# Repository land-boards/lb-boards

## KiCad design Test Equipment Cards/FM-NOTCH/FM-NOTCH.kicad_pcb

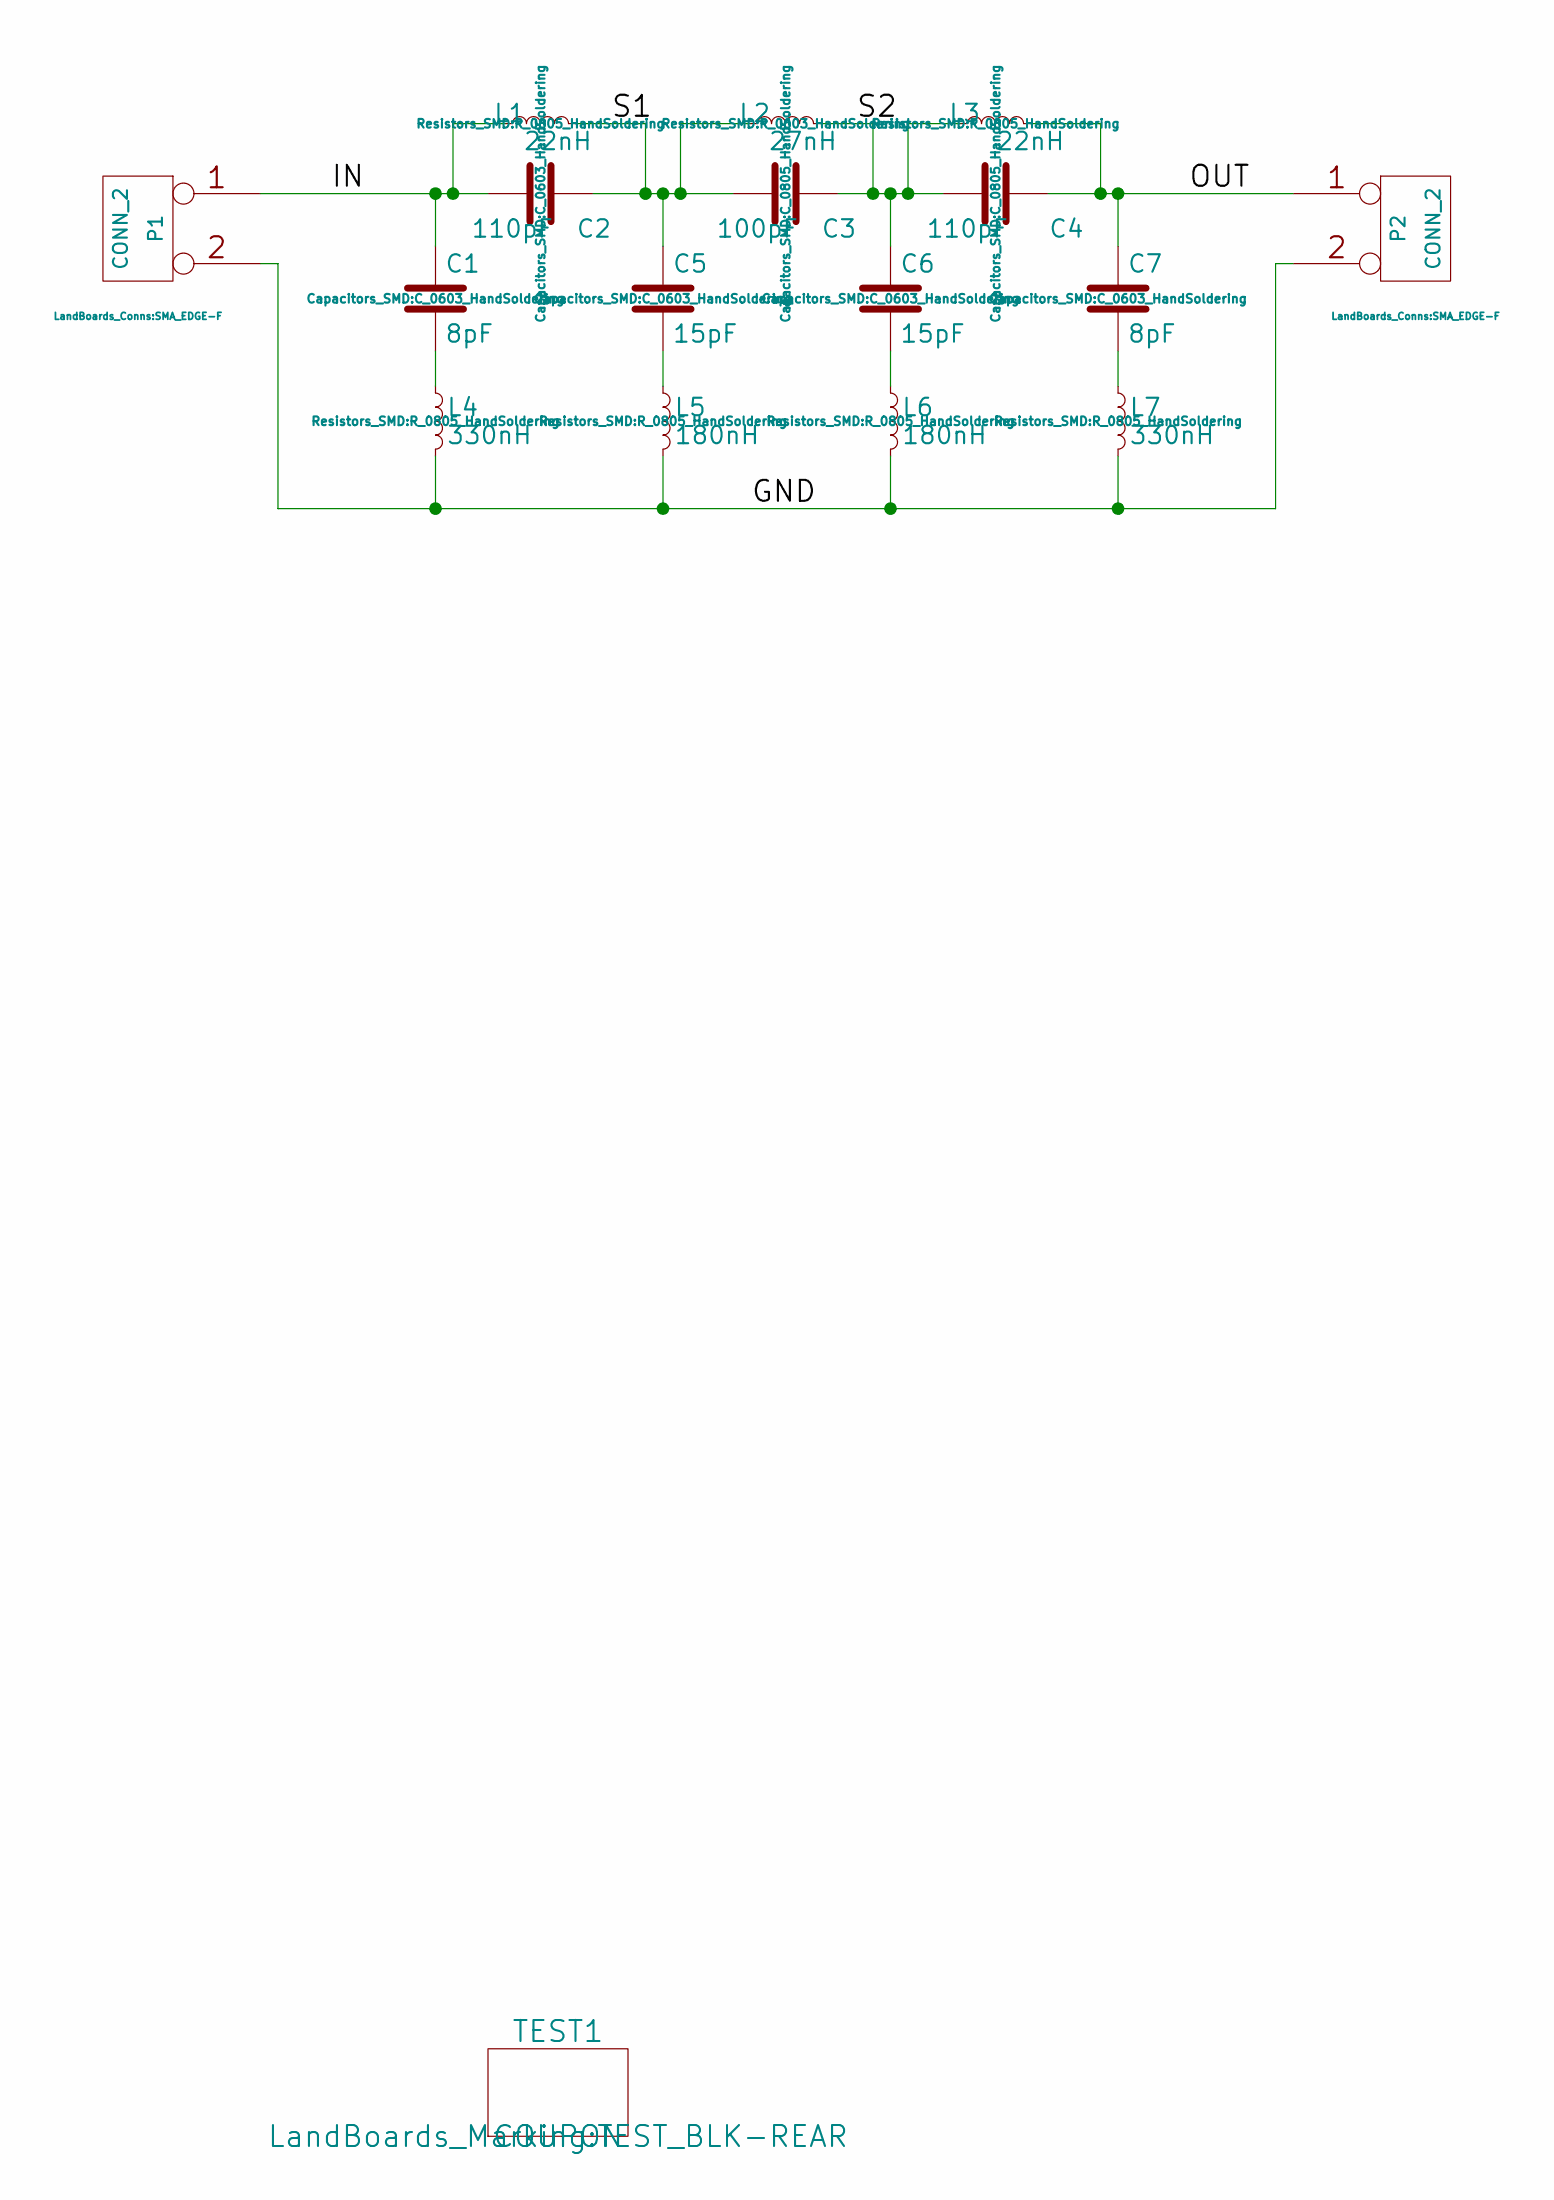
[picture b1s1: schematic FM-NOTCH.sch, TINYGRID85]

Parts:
C1, C7: 8pF; C_0603_HandSoldering
C2: 110pF; C_0603_HandSoldering
C3: 100pF; C_0805_HandSoldering
C4: 110pF; C_0805_HandSoldering
C5, C6: 15pF; C_0603_HandSoldering
L1, L3: 22nH; R_0805_HandSoldering
L2: 27nH; R_0603_HandSoldering
L4, L7: 330nH; R_0805_HandSoldering
L5, L6: 180nH; R_0805_HandSoldering
P1, P2: CONN_2; SMA_EDGE-F
TEST1: COUPON; TEST_BLK-REAR

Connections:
/GND: L4.2, L5.2, L6.2, L7.2, P1.2 (PM), P2.2 (PM)
/IN: C1.1, C2.2, L1.1, P1.1
/OUT: C4.1, C7.1, L3.2, P2.1
/S1: C2.1, C3.2, C5.1, L1.2, L2.1
/S2: C3.1, C4.2, C6.1, L2.2, L3.1
unnamed: C1.2, L4.1
unnamed: C5.2, L5.1
unnamed: C6.2, L6.1
unnamed: C7.2, L7.1

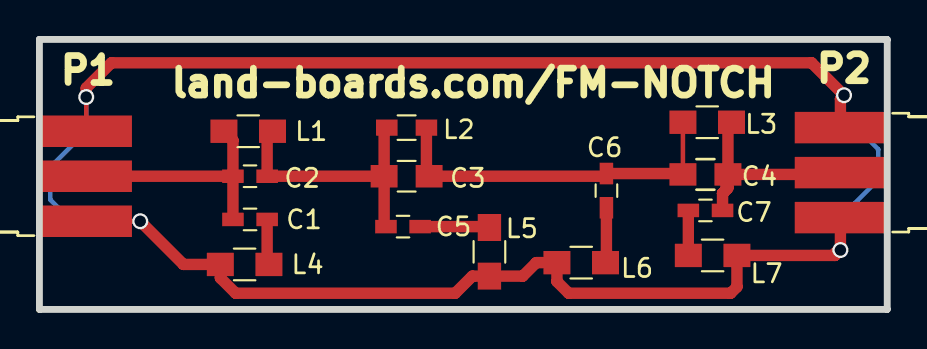
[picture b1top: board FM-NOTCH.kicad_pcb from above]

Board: 2 copper layers, 47.1 x 15.0 mm, 17 parts (0 on the bottom side), 9 nets.

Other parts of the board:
TEST: COUPON; TEST_BLK-REAR

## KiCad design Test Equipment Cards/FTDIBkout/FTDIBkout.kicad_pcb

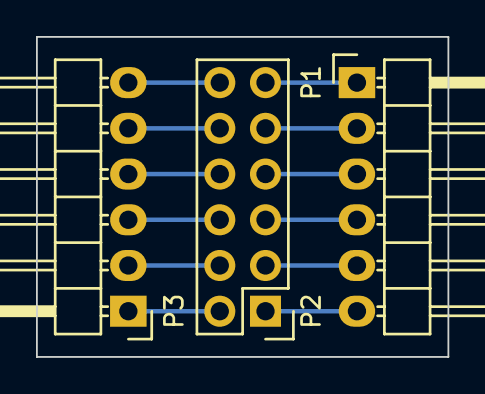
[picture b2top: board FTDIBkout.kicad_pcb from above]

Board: 2 copper layers, 22.9 x 17.8 mm, 3 parts (0 on the bottom side), 12 nets.

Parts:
P1, P3: CONN_01X06; Pin_Header_Angled_1x06
P2: CONN_02X06; Pin_Header_Straight_2x06

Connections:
unnamed: P1.1, P2.11
unnamed: P1.2, P2.9
unnamed: P1.3, P2.7
unnamed: P1.4, P2.5
unnamed: P1.5, P2.3
unnamed: P1.6, P2.1
unnamed: P2.2, P3.1
unnamed: P2.4, P3.2
unnamed: P2.6, P3.3
unnamed: P2.8, P3.4
unnamed: P2.10, P3.5
unnamed: P2.12, P3.6

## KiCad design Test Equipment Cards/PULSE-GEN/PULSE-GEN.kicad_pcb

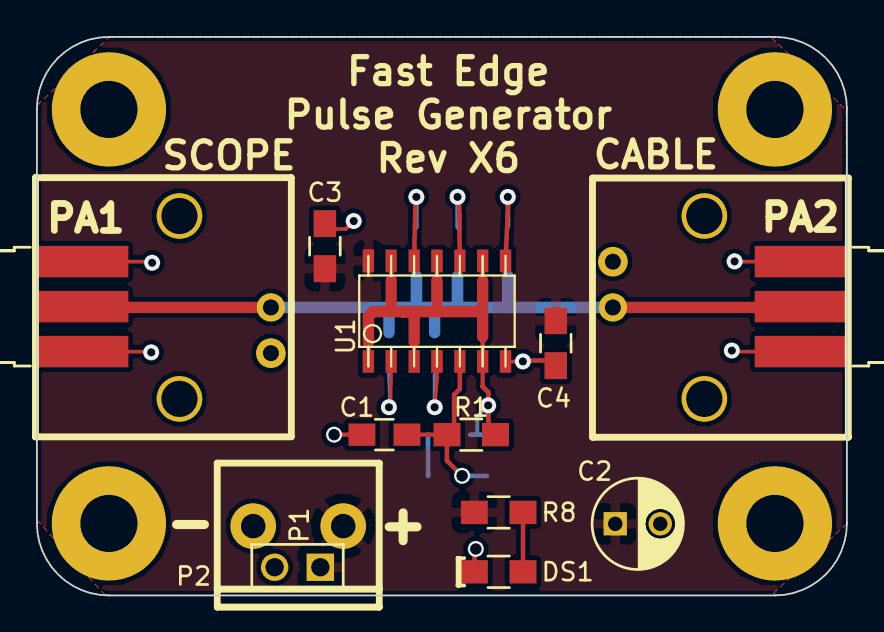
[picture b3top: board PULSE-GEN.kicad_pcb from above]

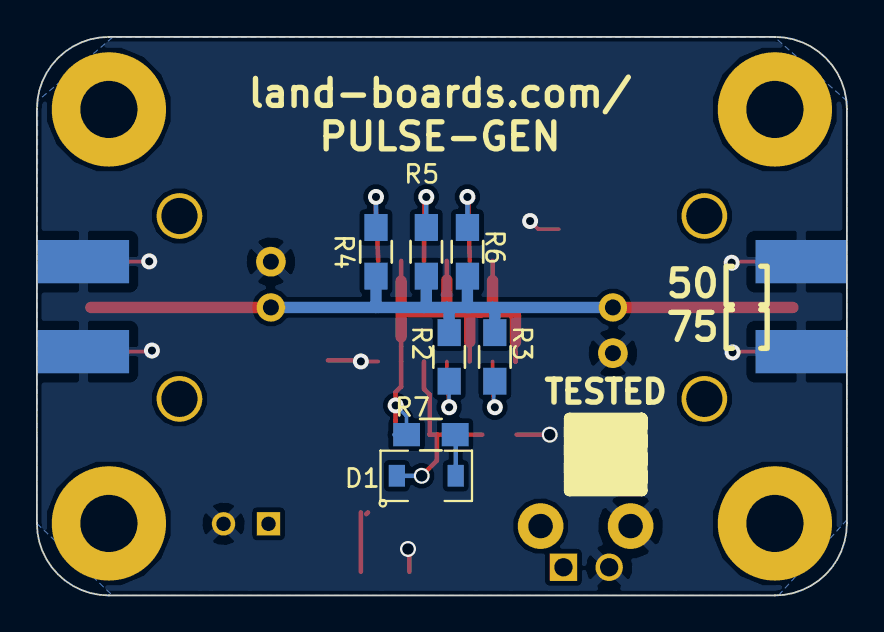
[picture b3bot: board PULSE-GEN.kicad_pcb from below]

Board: 2 copper layers, 45.0 x 31.0 mm, 26 parts (7 on the bottom side), 12 nets.

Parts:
C1: 47nF; C_0805_HandSoldering
C2: 47uF; C_Radial_D5_L11_P2.5
C3, C4: 0.1uF; C_0805_HandSoldering
D1: 1N4148; SOD-123
DS1: LED; R_0805_HandSoldering
MTG1, MTG2, MTG3, MTG4: CONN_1; MTG-4-40
P1: CONN_2; PIN_ARRAY_2X1
P2: CONN_2; TB2-5MM
PA1, PA2: SMA; SMA_EDGE-F
PB1, PB2: BNC; BNC-RT
R1: 33K; R_0805_HandSoldering
R2, R3, R4, R5, R6: 249; R_0805_HandSoldering
R7: 150; R_0805_HandSoldering
R8: 240; R_0805_HandSoldering
TESTED: VAL**; TEST_BLK-REAR
U1: 74AC14; so-14

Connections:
GND: C1.2, C2.2, C3.2, C4.2, DS1.2, P1.2, P2.2, PA1.2, PA2.2, PB1.2, PB2.2, U1.7
unnamed: C1.1, D1.1, R1.1, U1.5
unnamed: D1.2, R7.1
unnamed: DS1.1, R8.2
unnamed: PA1.1, PA2.1, PB1.1, PB2.1, R2.2, R3.2, R4.2, R5.2, R6.2
unnamed: R1.2, R7.2, U1.1, U1.3, U1.6, U1.9, U1.11, U1.13
unnamed: R2.1, U1.4
unnamed: R3.1, U1.2
unnamed: R4.1, U1.8
unnamed: R5.1, U1.10
unnamed: R6.1, U1.12
VCC: C2.1, C3.1, C4.1, P1.1, P2.1, R8.1, U1.14

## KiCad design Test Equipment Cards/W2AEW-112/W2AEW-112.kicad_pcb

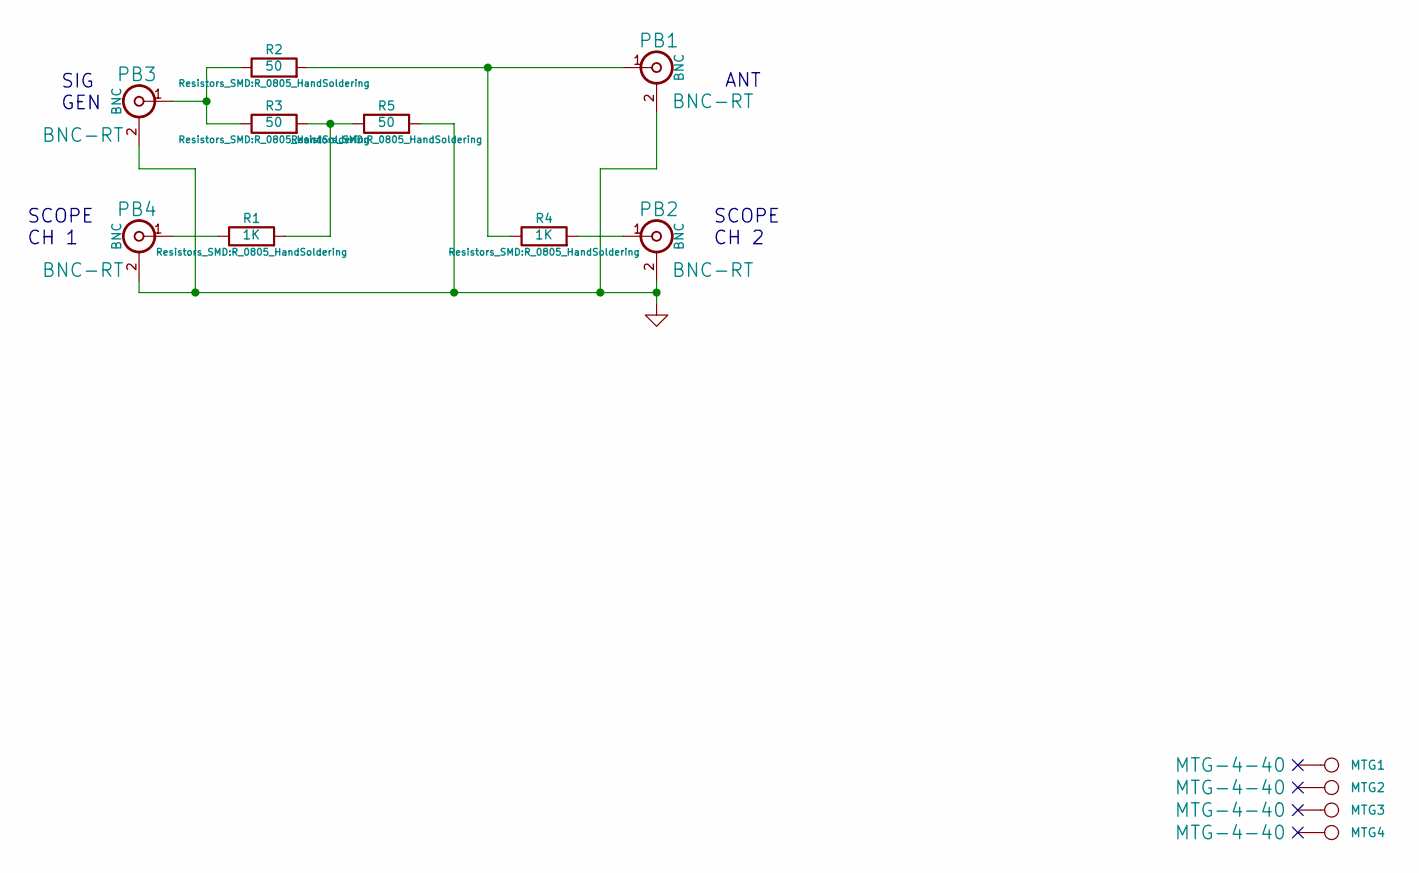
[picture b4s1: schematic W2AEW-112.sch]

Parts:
MTG1, MTG2, MTG3, MTG4: CONN_1; MTG-4-40
PB1, PB2, PB3, PB4: BNC; BNC-RT; MfgPN 31-5431-10RFX
R1, R4: 1K; R_0805_HandSoldering
R2, R3, R5: 50; R_0805_HandSoldering

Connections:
GND: PB1.2 (Ext), PB2.2 (Ext), PB3.2 (Ext), PB4.2 (Ext), R5.2
unnamed: PB1.1 (In), R2.2, R4.1
unnamed: PB2.1 (In), R4.2
unnamed: PB3.1 (In), R2.1, R3.1
unnamed: PB4.1 (In), R1.1
unnamed: R1.2, R3.2, R5.1

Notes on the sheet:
SIG GEN
ANT
SCOPE CH 1
SCOPE CH 2

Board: 2 copper layers, 13 parts (0 on the bottom side), 6 nets, no tracks yet.

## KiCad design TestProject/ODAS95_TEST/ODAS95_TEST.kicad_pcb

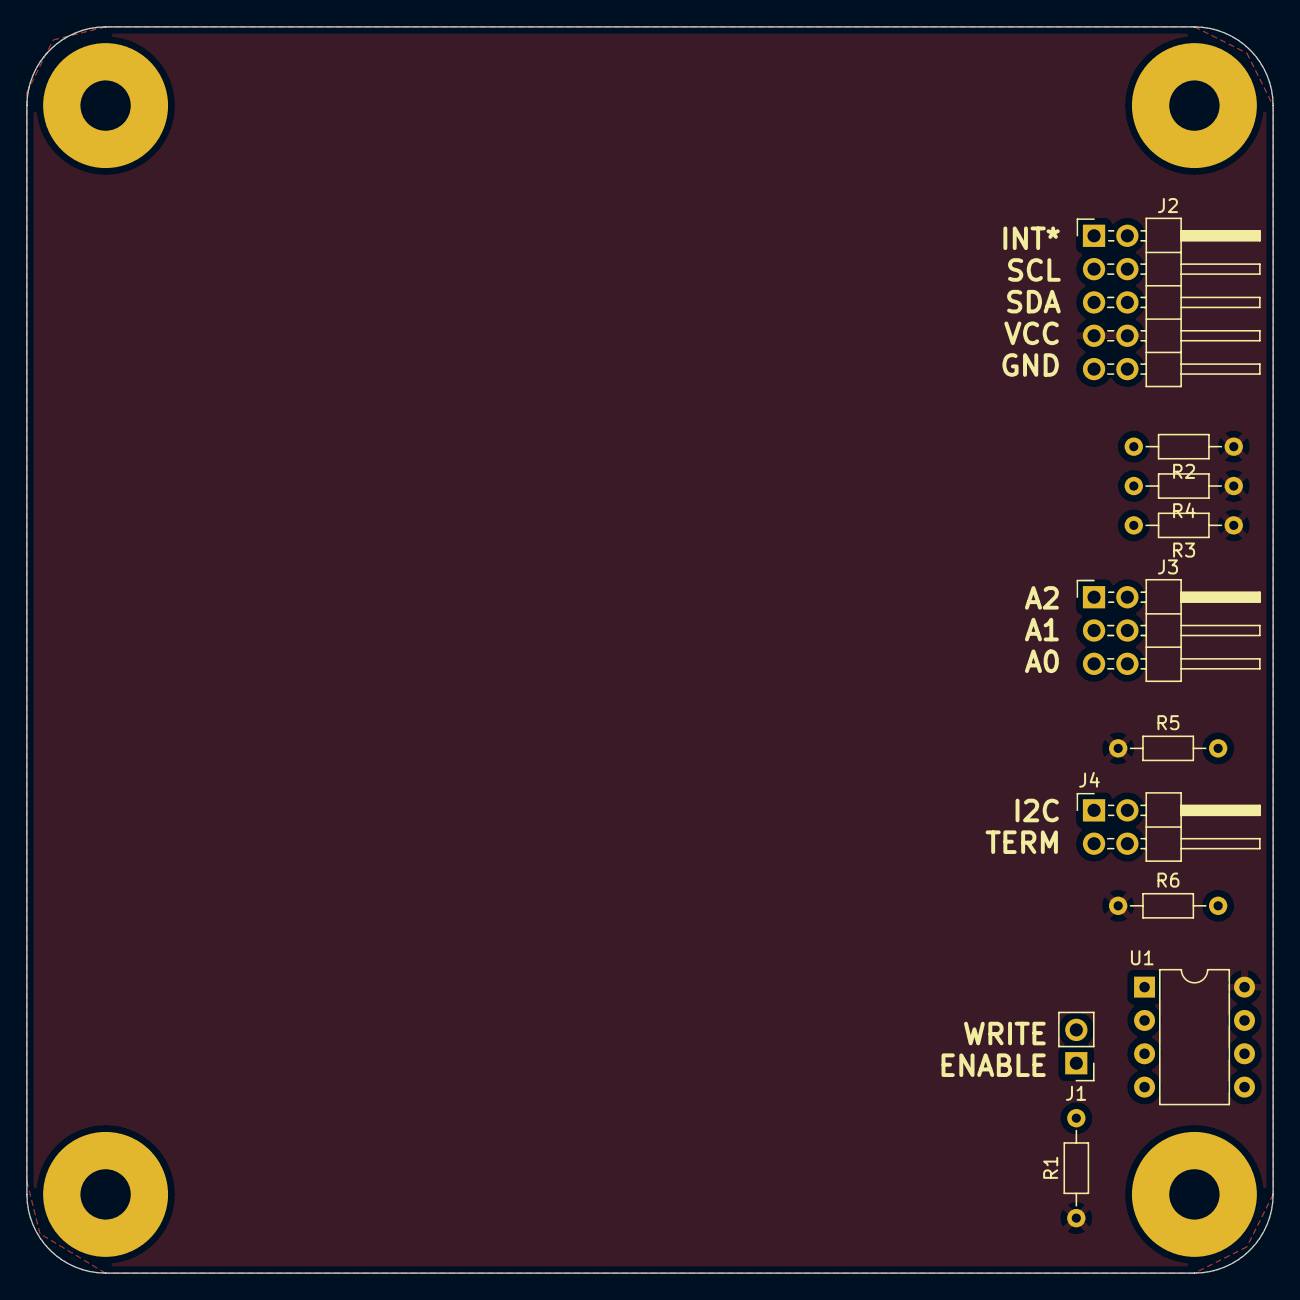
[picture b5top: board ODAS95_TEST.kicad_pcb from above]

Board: 2 copper layers, 95.0 x 95.0 mm, 16 parts (0 on the bottom side), 10 nets, no tracks yet.

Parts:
J1: Conn_01x02; PinHeader_1x02_P2.54mm_Vertical
J2: Conn_02x05_Odd_Even; PinHeader_2x05_P2.54mm_Horizontal
J3: Conn_02x03_Counter_Clockwise; PinHeader_2x03_P2.54mm_Horizontal
J4: Conn_02x02_Odd_Even; PinHeader_2x02_P2.54mm_Horizontal
MTG1, MTG2, MTG3, MTG4: MTG_HOLE; MTG-6-32
R1: 1K; R_Axial_DIN0204_L3.6mm_D1.6mm_P7.62mm_Horizontal
R2, R3, R4, R5, R6: 2.2K; R_Axial_DIN0204_L3.6mm_D1.6mm_P7.62mm_Horizontal
TEST1: TEST_COUPON; TEST_BLK-REAR
U1: 24lC024; DIP-8_W7.62mm

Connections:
/A0: J3.5, R4.2, U1.1 (A0)
/A1: J3.3, R3.2, U1.2 (A1)
/A2: J3.1, R2.2, U1.3 (A2)
/SCL: J2.3, J2.4, J4.3, U1.6 (SCL)
/SDA: J2.5, J2.6, J4.1, U1.5 (SDA)
GND: J1.2, J2.9, J2.10, J3.2, J3.4, J3.6, U1.4 (GND)
unnamed: J1.1, R1.2, U1.7 (~WP)
unnamed: J4.2, R5.2
unnamed: J4.4, R6.2
VCC: J2.7, J2.8, R1.1, R2.1, R3.1, R4.1, R5.1, R6.1, U1.8 (VCC)

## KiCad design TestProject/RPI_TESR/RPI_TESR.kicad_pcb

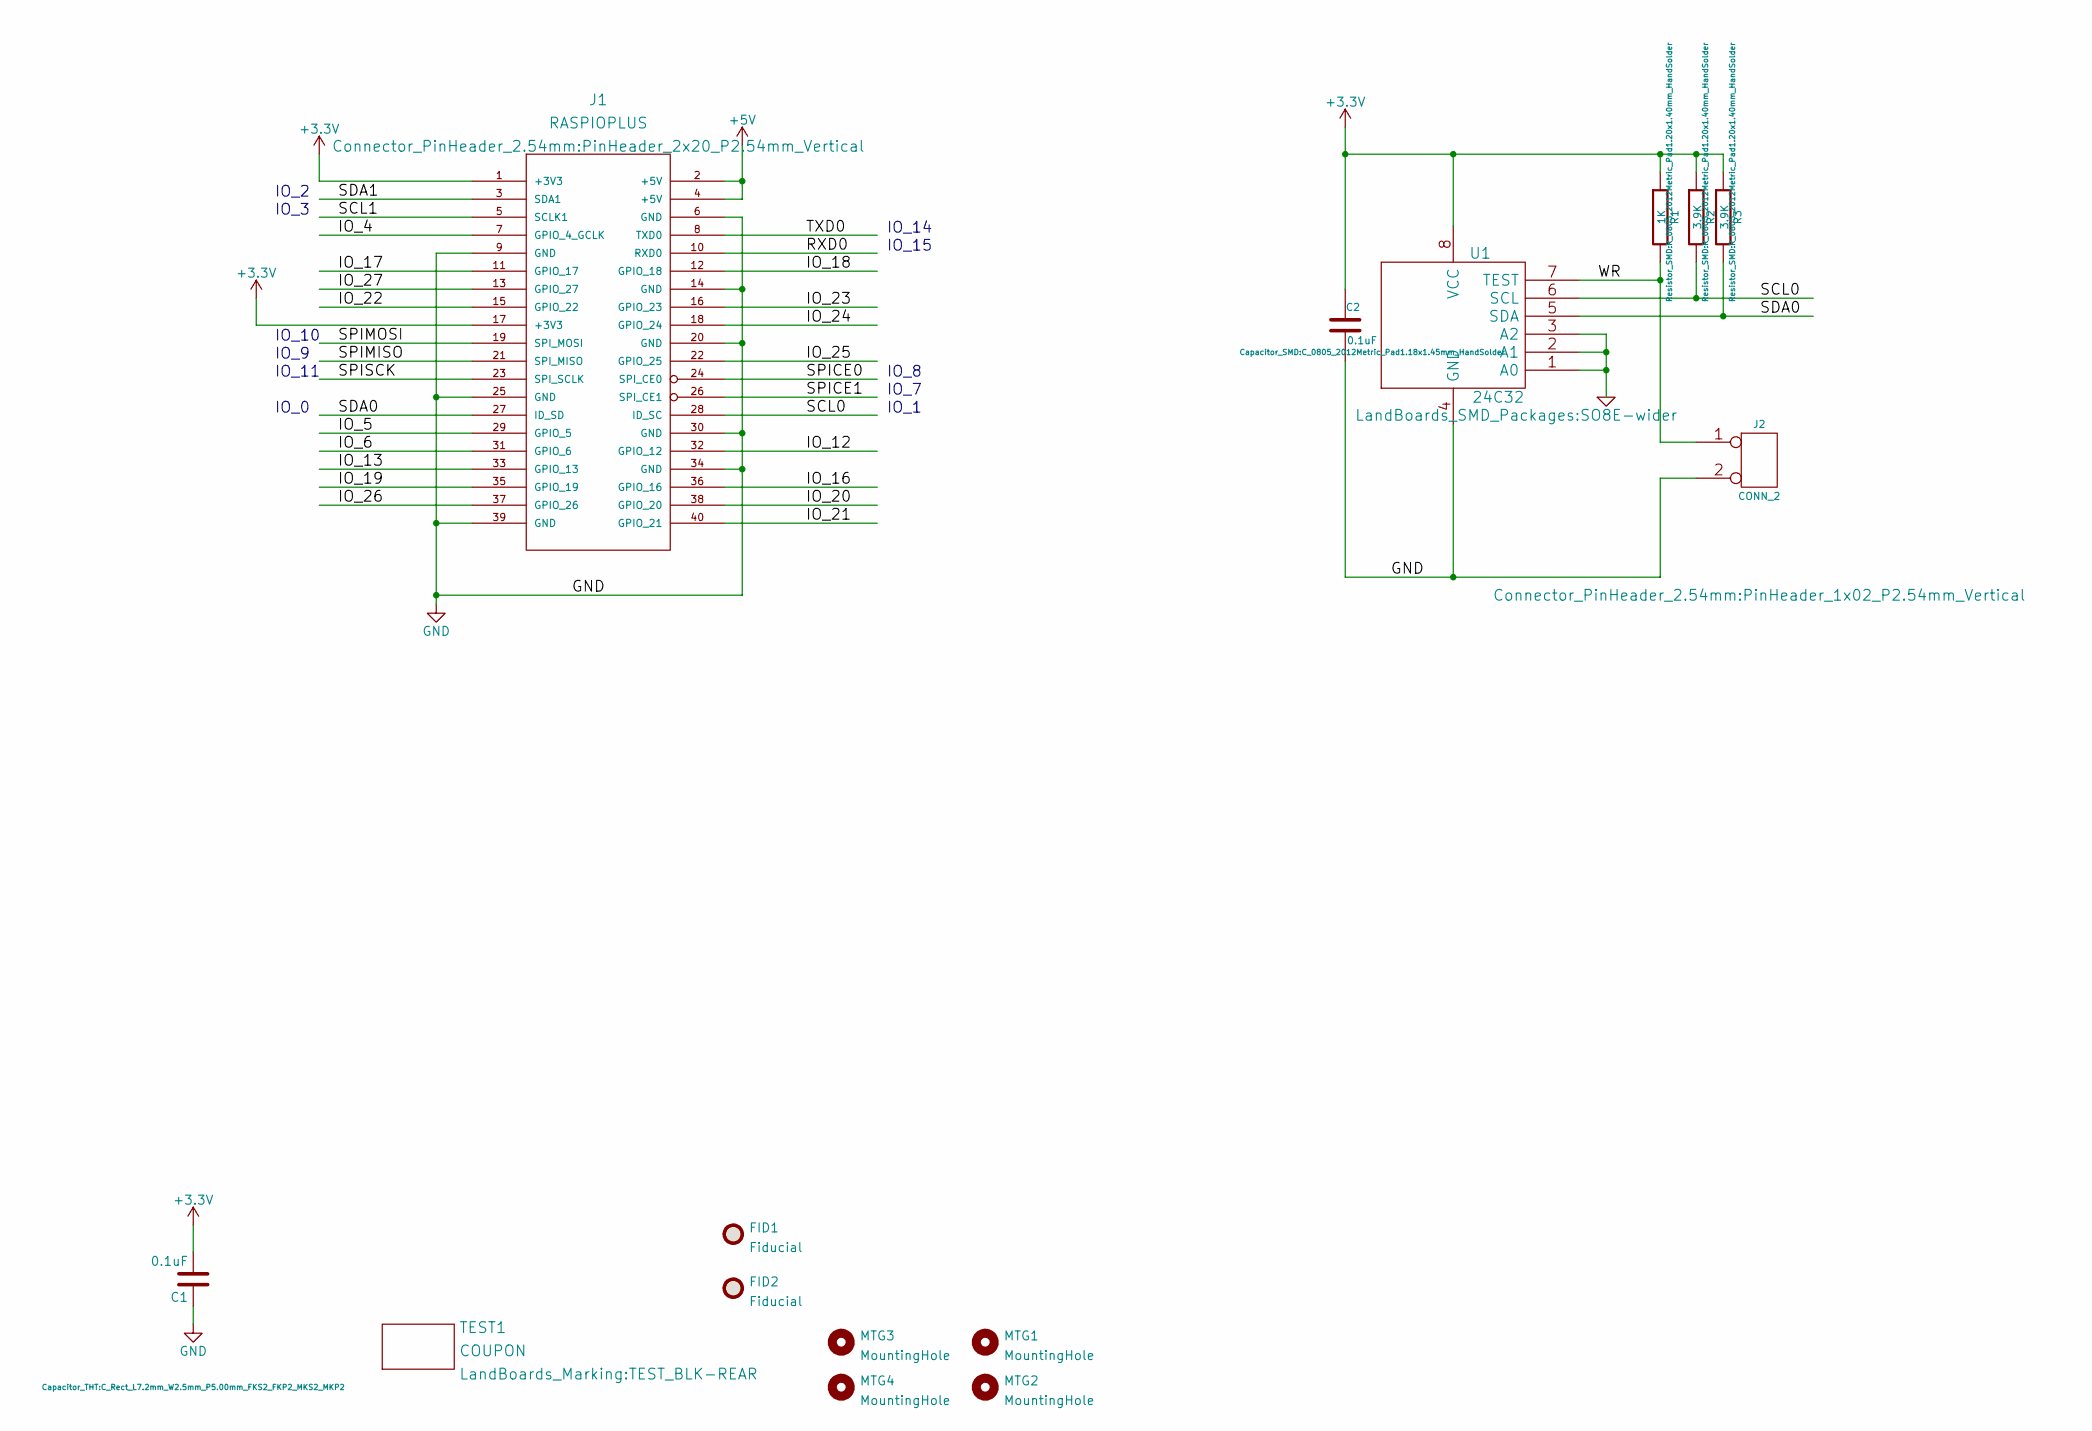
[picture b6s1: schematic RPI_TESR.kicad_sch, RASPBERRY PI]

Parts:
C1: 0.1uF; C_Rect_L7.2mm_W2.5mm_P5.00mm_FKS2_FKP2_MKS2_MKP2
C2: 0.1uF; C_0805_2012Metric_Pad1.18x1.45mm_HandSolder
FID1, FID2: Fiducial; Fiducial_0.75mm_Mask2.25mm
J1: RASPIOPLUS; PinHeader_2x20_P2.54mm_Vertical
J2: CONN_2; PinHeader_1x02_P2.54mm_Vertical
MTG1, MTG2, MTG3, MTG4: MountingHole; MountingHole_2.7mm_M2.5
R1: 1K; R_0805_2012Metric_Pad1.20x1.40mm_HandSolder
R2, R3: 3.9K; R_0805_2012Metric_Pad1.20x1.40mm_HandSolder
TEST1: COUPON; TEST_BLK-REAR
U1: 24C32; SO8E-wider

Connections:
+3V3: C1.2, C2.1, J1.1 (+3V3), J1.17 (+3V3), R1.1, R2.1, R3.1, U1.8 (VCC)
+5V: J1.2 (+5V), J1.4 (+5V)
/IO_4: J1.7 (GPIO_4_GCLK)
/IO_5: J1.29 (GPIO_5)
/IO_6: J1.31 (GPIO_6)
/IO_12: J1.32 (GPIO_12)
/IO_13: J1.33 (GPIO_13)
/IO_16: J1.36 (GPIO_16)
/IO_17: J1.11 (GPIO_17)
/IO_18: J1.12 (GPIO_18)
/IO_19: J1.35 (GPIO_19)
/IO_20: J1.38 (GPIO_20)
/IO_21: J1.40 (GPIO_21)
/IO_22: J1.15 (GPIO_22)
/IO_23: J1.16 (GPIO_23)
/IO_24: J1.18 (GPIO_24)
/IO_25: J1.22 (GPIO_25)
/IO_26: J1.37 (GPIO_26)
/IO_27: J1.13 (GPIO_27)
/RXD0: J1.10 (RXD0)
/SCL0: J1.28 (ID_SC), R2.2, U1.6 (SCL)
/SCL1: J1.5 (SCLK1)
/SDA0: J1.27 (ID_SD), R3.2, U1.5 (SDA)
/SDA1: J1.3 (SDA1)
/SPICE0: J1.24 (SPI_CE0)
/SPICE1: J1.26 (SPI_CE1)
/SPIMISO: J1.21 (SPI_MISO)
/SPIMOSI: J1.19 (SPI_MOSI)
/SPISCK: J1.23 (SPI_SCLK)
/TXD0: J1.8 (TXD0)
/WR: J2.1, R1.2, U1.7 (TEST)
GND: C1.1, C2.2, J1.6 (GND), J1.9 (GND), J1.14 (GND), J1.20 (GND), J1.25 (GND), J1.30 (GND), J1.34 (GND), J1.39 (GND), J2.2 (PM), U1.1 (A0), U1.2 (A1), U1.3 (A2), U1.4 (GND)

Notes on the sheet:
IO_14
IO_7
IO_15
IO_2
IO_11
IO_9
IO_8
IO_0
IO_10
IO_3
IO_1

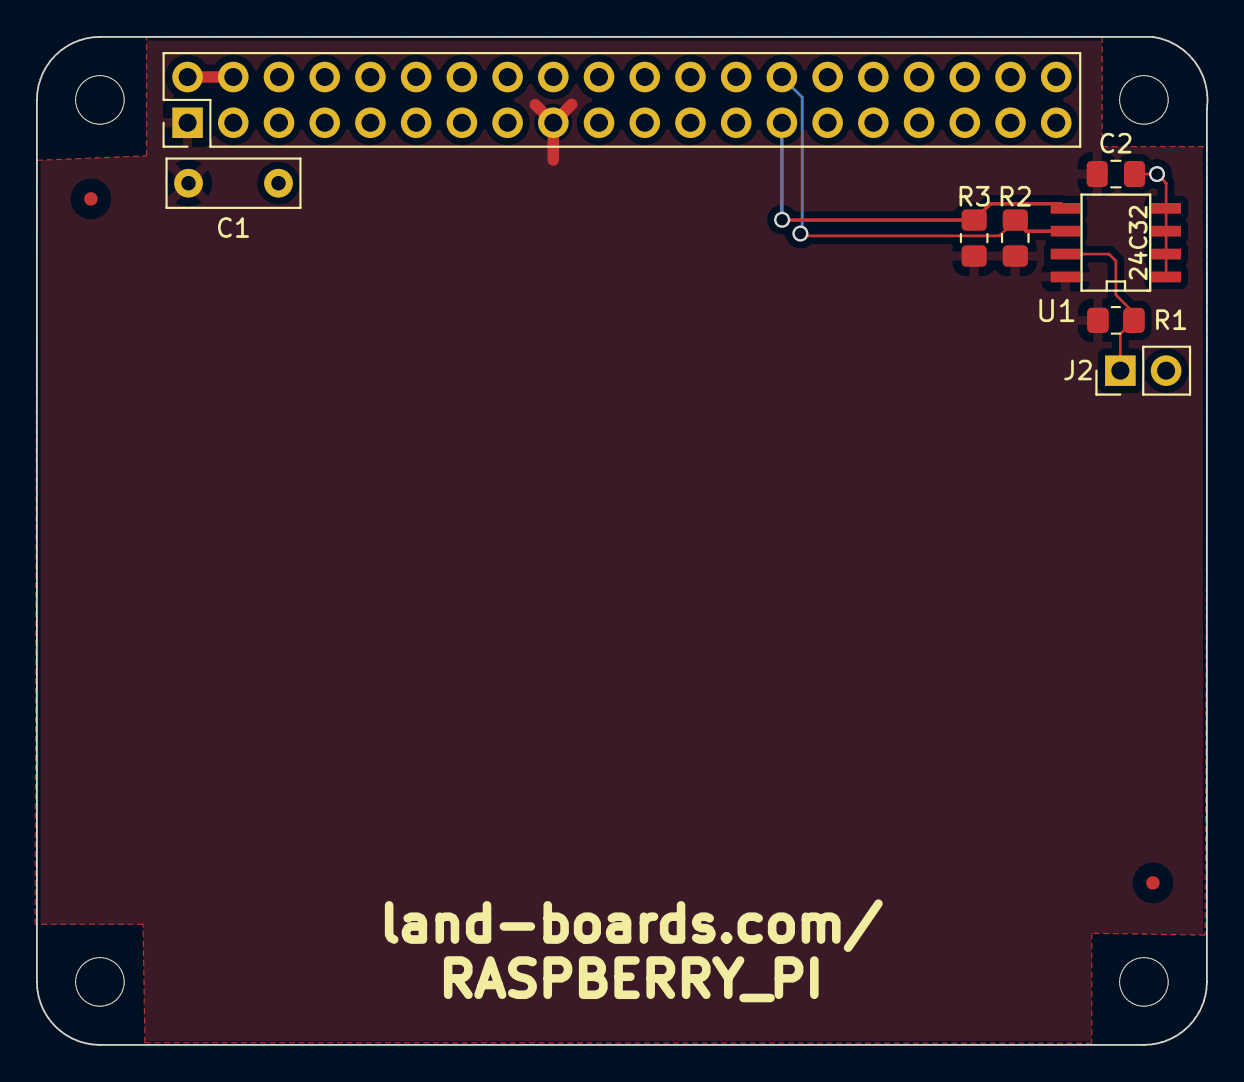
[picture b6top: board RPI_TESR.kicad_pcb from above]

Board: 2 copper layers, 65.0 x 56.0 mm, 15 parts (0 on the bottom side), 6 nets.
